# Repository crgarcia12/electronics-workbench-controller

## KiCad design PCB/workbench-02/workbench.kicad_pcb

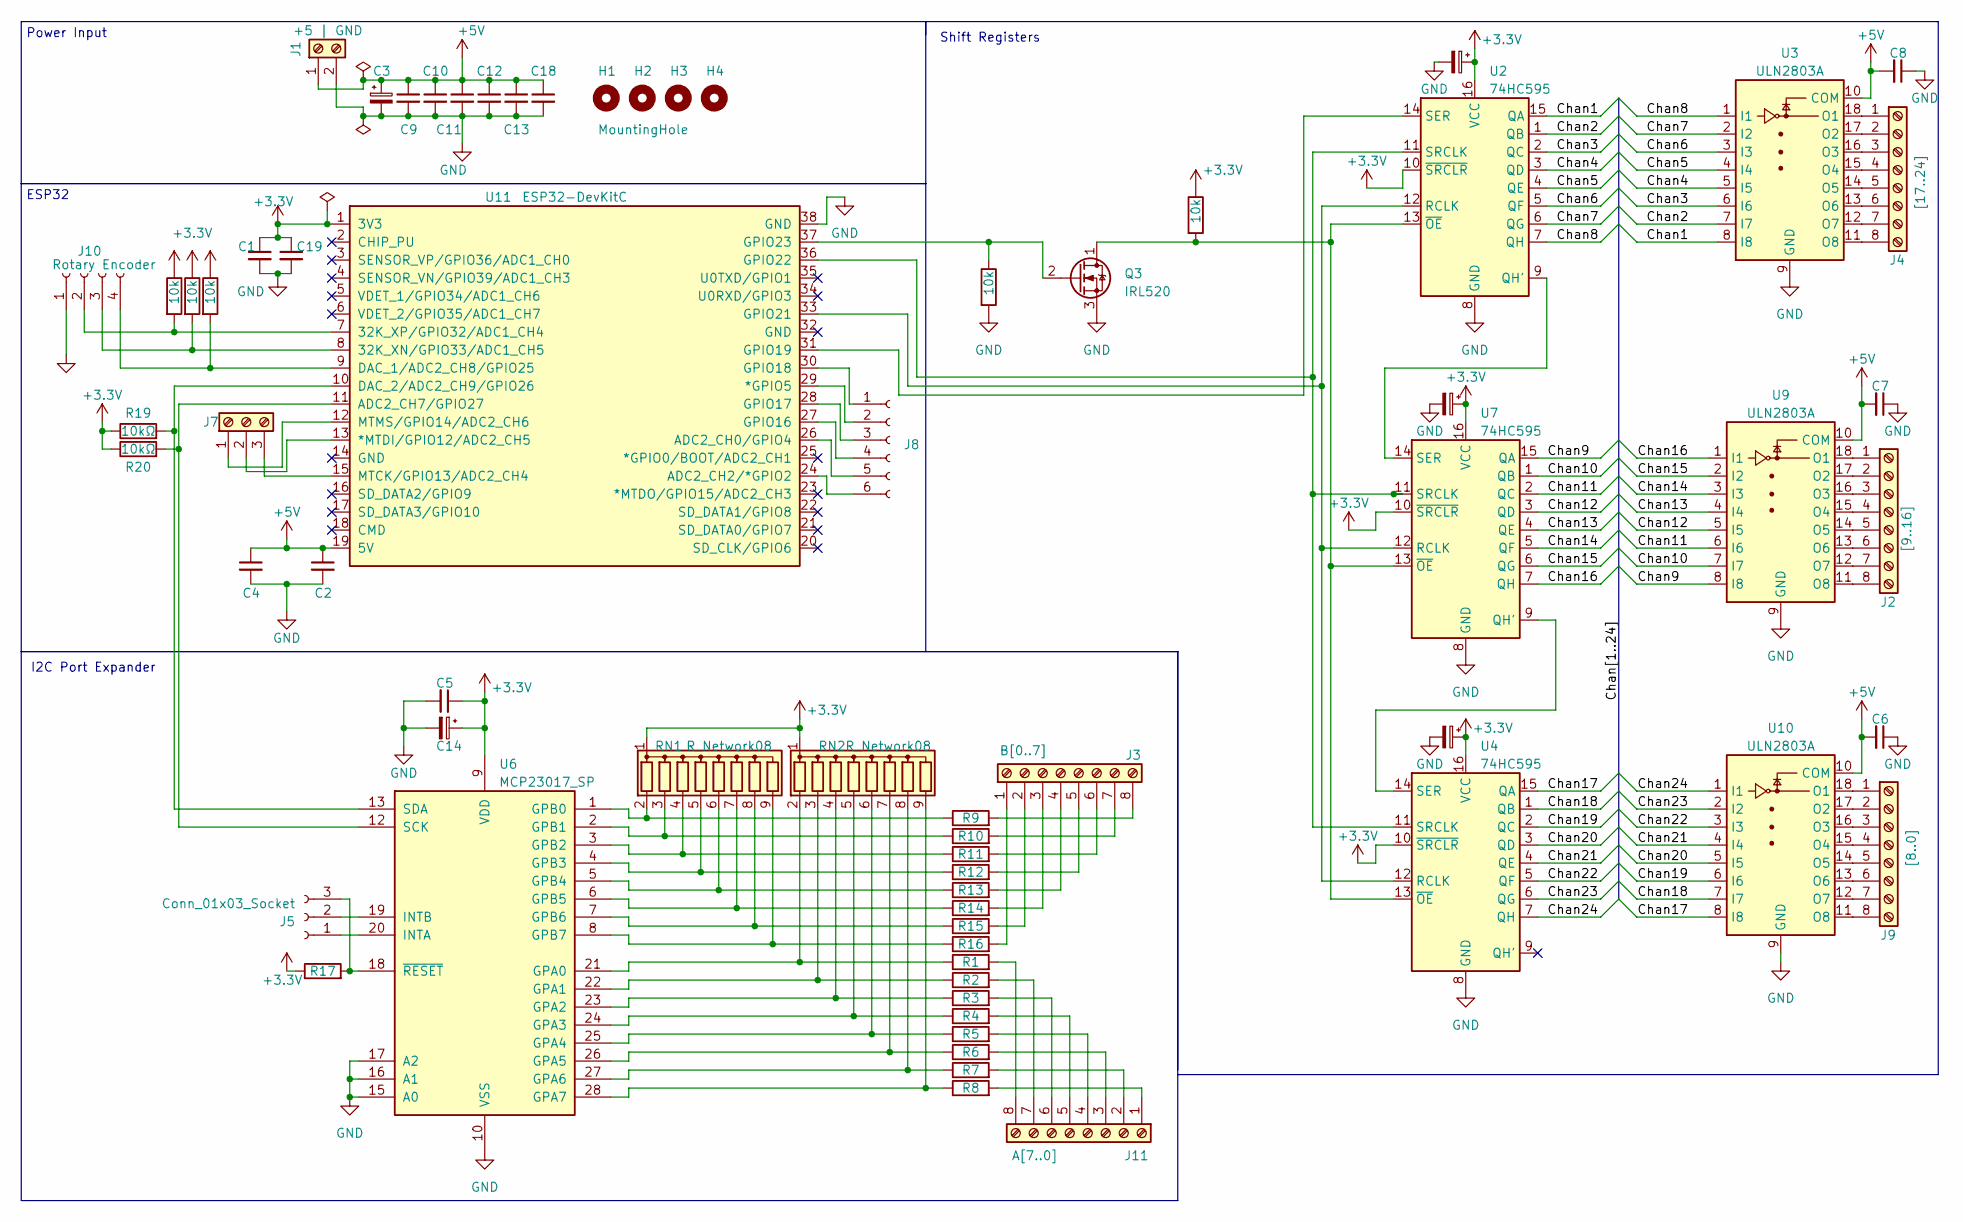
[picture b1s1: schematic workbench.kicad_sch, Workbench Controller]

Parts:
C1, C2: C; C_Disc_D5.1mm_W3.2mm_P5.00mm
C3, C14, C15, C16, C17: 10uF; CP_Radial_D6.3mm_P2.50mm
C4, C5, C6, C7, C8, C9, C10, C11, C12, C13, C18, C19: C; C_1210_3225Metric_Pad1.33x2.70mm_HandSolder
H1, H2, H4: MountingHole; MountingHole_4.3mm_M4_Pad_Via
H3: MountingHole; MountingHole_4.3mm_M4_DIN965_Pad
J1: +5 | GND; TerminalBlock_Phoenix_MKDS-3-2-5.08_1x02_P5.08mm_Horizontal
J2: [9..16]; TerminalBlock_Phoenix_MKDS-3-8-5.08_1x08_P5.08mm_Horizontal
J3: B[0..7]; TerminalBlock_Phoenix_MKDS-3-8-5.08_1x08_P5.08mm_Horizontal
J4: [17..24]; TerminalBlock_Phoenix_MKDS-3-8-5.08_1x08_P5.08mm_Horizontal
J5: Conn_01x03_Socket; PinHeader_1x03_P2.54mm_Vertical
J7: Led-13-12-14; TerminalBlock_Phoenix_MKDS-3-3-5.08_1x03_P5.08mm_Horizontal
J8: Conn_01x06_Socket; PinHeader_1x06_P2.54mm_Vertical
J9: [8..0]; TerminalBlock_Phoenix_MKDS-3-8-5.08_1x08_P5.08mm_Horizontal
J10: Rotary Encoder; TerminalBlock_Phoenix_MKDS-3-4-5.08_1x04_P5.08mm_Horizontal
J11: A[7..0]; TerminalBlock_Phoenix_MKDS-3-8-5.08_1x08_P5.08mm_Horizontal
Q3: IRL520; TO-220-3_Vertical
R1, R2, R3, R4, R5, R6, R7, R8, R9, R10, R11, R12, R13, R14, R15, R16, R17: R; R_Axial_DIN0207_L6.3mm_D2.5mm_P7.62mm_Horizontal
R19, R20: 10kΩ; R_Axial_DIN0207_L6.3mm_D2.5mm_P7.62mm_Horizontal; JLCPCB C25804
R21, R22, R35, R52, R53: 10k; R_Axial_DIN0207_L6.3mm_D2.5mm_P7.62mm_Horizontal
RN1, RN2: R_Network08; R_Array_SIP9
U2, U4, U7: 74HC595; DIP-16_W7.62mm_Socket_LongPads
U3, U9, U10: ULN2803A; DIP-18_W7.62mm_LongPads
U6: MCP23017_SP; DIP-28_W7.62mm
U11: ESP32-DevKitC

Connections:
+3.3V: C1.1, C5.1, C14.1, C15.1, C16.1, C17.1, C19.1, R17.1, R19.1, R20.1, R21.1, R22.1, R35.1, R53.1, RN1.1 (common), RN2.1 (common), U2.10 (~SRCLR), U2.16 (VCC), U4.10 (~SRCLR), U4.16 (VCC), U6.9 (VDD), U7.10 (~SRCLR), U7.16 (VCC), U11.1 (3V3)
+5V: C2.1, C3.1, C4.1, C6.2, C7.2, C8.2, C9.1, C10.1, C11.1, C12.1, C13.1, C18.1, J1.1, U3.10 (COM), U9.10 (COM), U10.10 (COM), U11.19 (5V)
/Chan1: U2.15 (QA), U3.8 (I8)
/Chan2: U2.1 (QB), U3.7 (I7)
/Chan3: U2.2 (QC), U3.6 (I6)
/Chan4: U2.3 (QD), U3.5 (I5)
/Chan5: U2.4 (QE), U3.4 (I4)
/Chan6: U2.5 (QF), U3.3 (I3)
/Chan7: U2.6 (QG), U3.2 (I2)
/Chan8: U2.7 (QH), U3.1 (I1)
/Chan9: U7.15 (QA), U9.8 (I8)
/Chan10: U7.1 (QB), U9.7 (I7)
/Chan11: U7.2 (QC), U9.6 (I6)
/Chan12: U7.3 (QD), U9.5 (I5)
/Chan13: U7.4 (QE), U9.4 (I4)
/Chan14: U7.5 (QF), U9.3 (I3)
/Chan15: U7.6 (QG), U9.2 (I2)
/Chan16: U7.7 (QH), U9.1 (I1)
/Chan17: U4.15 (QA), U10.8 (I8)
/Chan18: U4.1 (QB), U10.7 (I7)
/Chan19: U4.2 (QC), U10.6 (I6)
/Chan20: U4.3 (QD), U10.5 (I5)
/Chan21: U4.4 (QE), U10.4 (I4)
/Chan22: U4.5 (QF), U10.3 (I3)
/Chan23: U4.6 (QG), U10.2 (I2)
/Chan24: U4.7 (QH), U10.1 (I1)
GND: C1.2, C2.2, C3.2, C4.2, C5.2, C6.1, C7.1, C8.1, C9.2, C10.2, C11.2, C12.2, C13.2, C14.2, C15.2, C16.2, C17.2, C18.2, C19.2, J1.2, J10.1, Q3.3 (S), R52.2, U2.8 (GND), U3.9 (GND), U4.8 (GND), U6.10 (VSS), U6.15 (A0), U6.16 (A1), U6.17 (A2), U7.8 (GND), U9.9 (GND), U10.9 (GND), U11.38 (GND)
unnamed: J2.1, U9.18 (O1)
unnamed: J2.2, U9.17 (O2)
unnamed: J2.3, U9.16 (O3)
unnamed: J2.4, U9.15 (O4)
unnamed: J2.5, U9.14 (O5)
unnamed: J2.6, U9.13 (O6)
unnamed: J2.7, U9.12 (O7)
unnamed: J2.8, U9.11 (O8)
unnamed: J3.1, R16.2
unnamed: J3.2, R15.2
unnamed: J3.3, R14.2
unnamed: J3.4, R13.2
unnamed: J3.5, R12.2
unnamed: J3.6, R11.2
unnamed: J3.7, R10.2
unnamed: J3.8, R9.2
unnamed: J4.1, U3.18 (O1)
unnamed: J4.2, U3.17 (O2)
unnamed: J4.3, U3.16 (O3)
unnamed: J4.4, U3.15 (O4)
unnamed: J4.5, U3.14 (O5)
unnamed: J4.6, U3.13 (O6)
unnamed: J4.7, U3.12 (O7)
unnamed: J4.8, U3.11 (O8)
unnamed: J5.1, U6.20 (INTA)
unnamed: J5.2, U6.19 (INTB)
unnamed: J5.3, R17.2, U6.18 (~RESET)
unnamed: J7.1, U11.12 (MTMS/GPIO14/ADC2_CH6)
unnamed: J7.2, U11.13 (*MTDI/GPIO12/ADC2_CH5)
unnamed: J7.3, U11.15 (MTCK/GPIO13/ADC2_CH4)
unnamed: J8.1, U11.30 (GPIO18)
unnamed: J8.2, U11.29 (*GPIO5)
unnamed: J8.3, U11.28 (GPIO17)
unnamed: J8.4, U11.27 (GPIO16)
unnamed: J8.5, U11.26 (ADC2_CH0/GPIO4)
unnamed: J8.6, U11.24 (ADC2_CH2/*GPIO2)
unnamed: J9.1, U10.18 (O1)
unnamed: J9.2, U10.17 (O2)
unnamed: J9.3, U10.16 (O3)
unnamed: J9.4, U10.15 (O4)
unnamed: J9.5, U10.14 (O5)
unnamed: J9.6, U10.13 (O6)
unnamed: J9.7, U10.12 (O7)
unnamed: J9.8, U10.11 (O8)
unnamed: J10.2, R21.2, U11.7 (32K_XP/GPIO32/ADC1_CH4)
unnamed: J10.3, R22.2, U11.8 (32K_XN/GPIO33/ADC1_CH5)
unnamed: J10.4, R35.2, U11.9 (DAC_1/ADC2_CH8/GPIO25)
unnamed: J11.1, R8.2
unnamed: J11.2, R7.2
unnamed: J11.3, R6.2
unnamed: J11.4, R5.2
unnamed: J11.5, R4.2
unnamed: J11.6, R3.2
unnamed: J11.7, R2.2
unnamed: J11.8, R1.2
unnamed: Q3.1 (D), R53.2, U2.13 (~OE), U4.13 (~OE), U7.13 (~OE)
unnamed: Q3.2 (G), R52.1, U11.37 (GPIO23)
unnamed: R9.1, RN1.2 (R1), U6.1 (GPB0)
unnamed: R10.1, RN1.3 (R2), U6.2 (GPB1)
unnamed: R11.1, RN1.4 (R3), U6.3 (GPB2)
unnamed: R12.1, RN1.5 (R4), U6.4 (GPB3)
unnamed: R13.1, RN1.6 (R5), U6.5 (GPB4)
unnamed: R14.1, RN1.7 (R6), U6.6 (GPB5)
unnamed: R15.1, RN1.8 (R7), U6.7 (GPB6)
unnamed: R16.1, RN1.9 (R8), U6.8 (GPB7)
unnamed: R1.1, RN2.2 (R1), U6.21 (GPA0)
unnamed: R2.1, RN2.3 (R2), U6.22 (GPA1)
unnamed: R3.1, RN2.4 (R3), U6.23 (GPA2)
unnamed: R4.1, RN2.5 (R4), U6.24 (GPA3)
unnamed: R5.1, RN2.6 (R5), U6.25 (GPA4)
unnamed: R6.1, RN2.7 (R6), U6.26 (GPA5)
unnamed: R7.1, RN2.8 (R7), U6.27 (GPA6)
unnamed: R8.1, RN2.9 (R8), U6.28 (GPA7)
unnamed: U2.9 (QH'), U7.14 (SER)
unnamed: U4.14 (SER), U7.9 (QH')
unnamed: R20.2, U6.12 (SCK), U11.11 (ADC2_CH7/GPIO27)
unnamed: R19.2, U6.13 (SDA), U11.10 (DAC_2/ADC2_CH9/GPIO26)
unnamed: U2.14 (SER), U11.31 (GPIO19)
unnamed: U2.12 (RCLK), U4.12 (RCLK), U7.12 (RCLK), U11.33 (GPIO21)
unnamed: U2.11 (SRCLK), U4.11 (SRCLK), U7.11 (SRCLK), U11.36 (GPIO22)

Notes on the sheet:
ESP32
Power Input
Shift Registers
I2C Port Expander

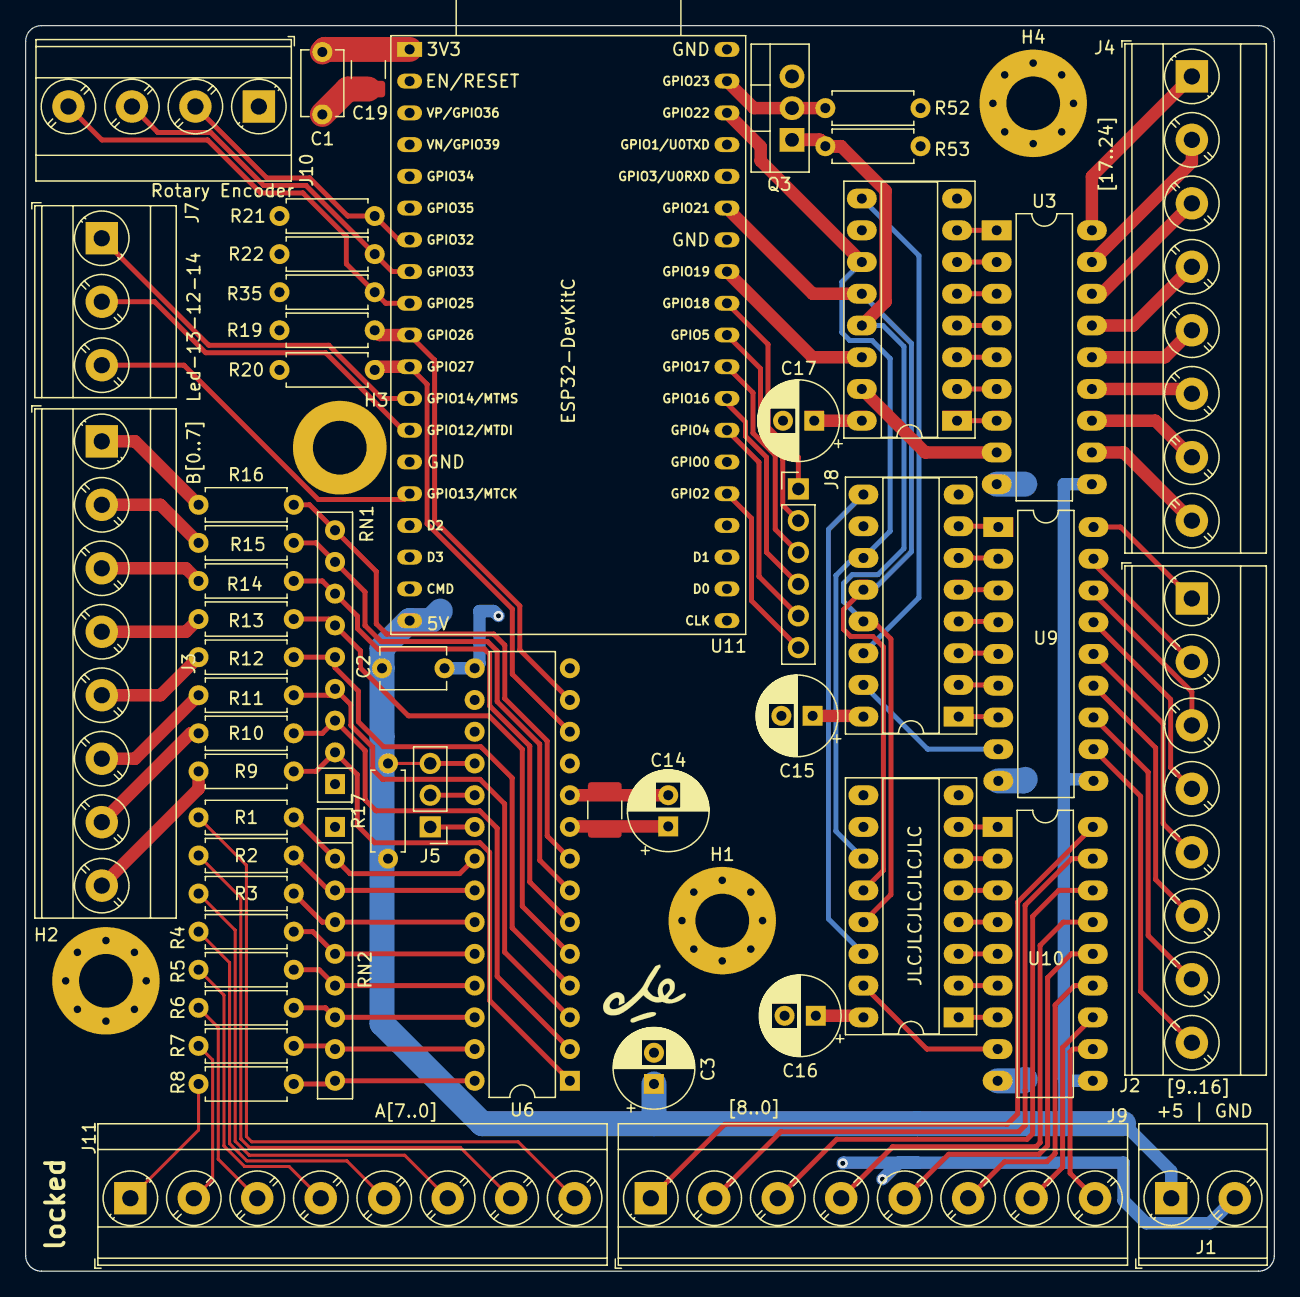
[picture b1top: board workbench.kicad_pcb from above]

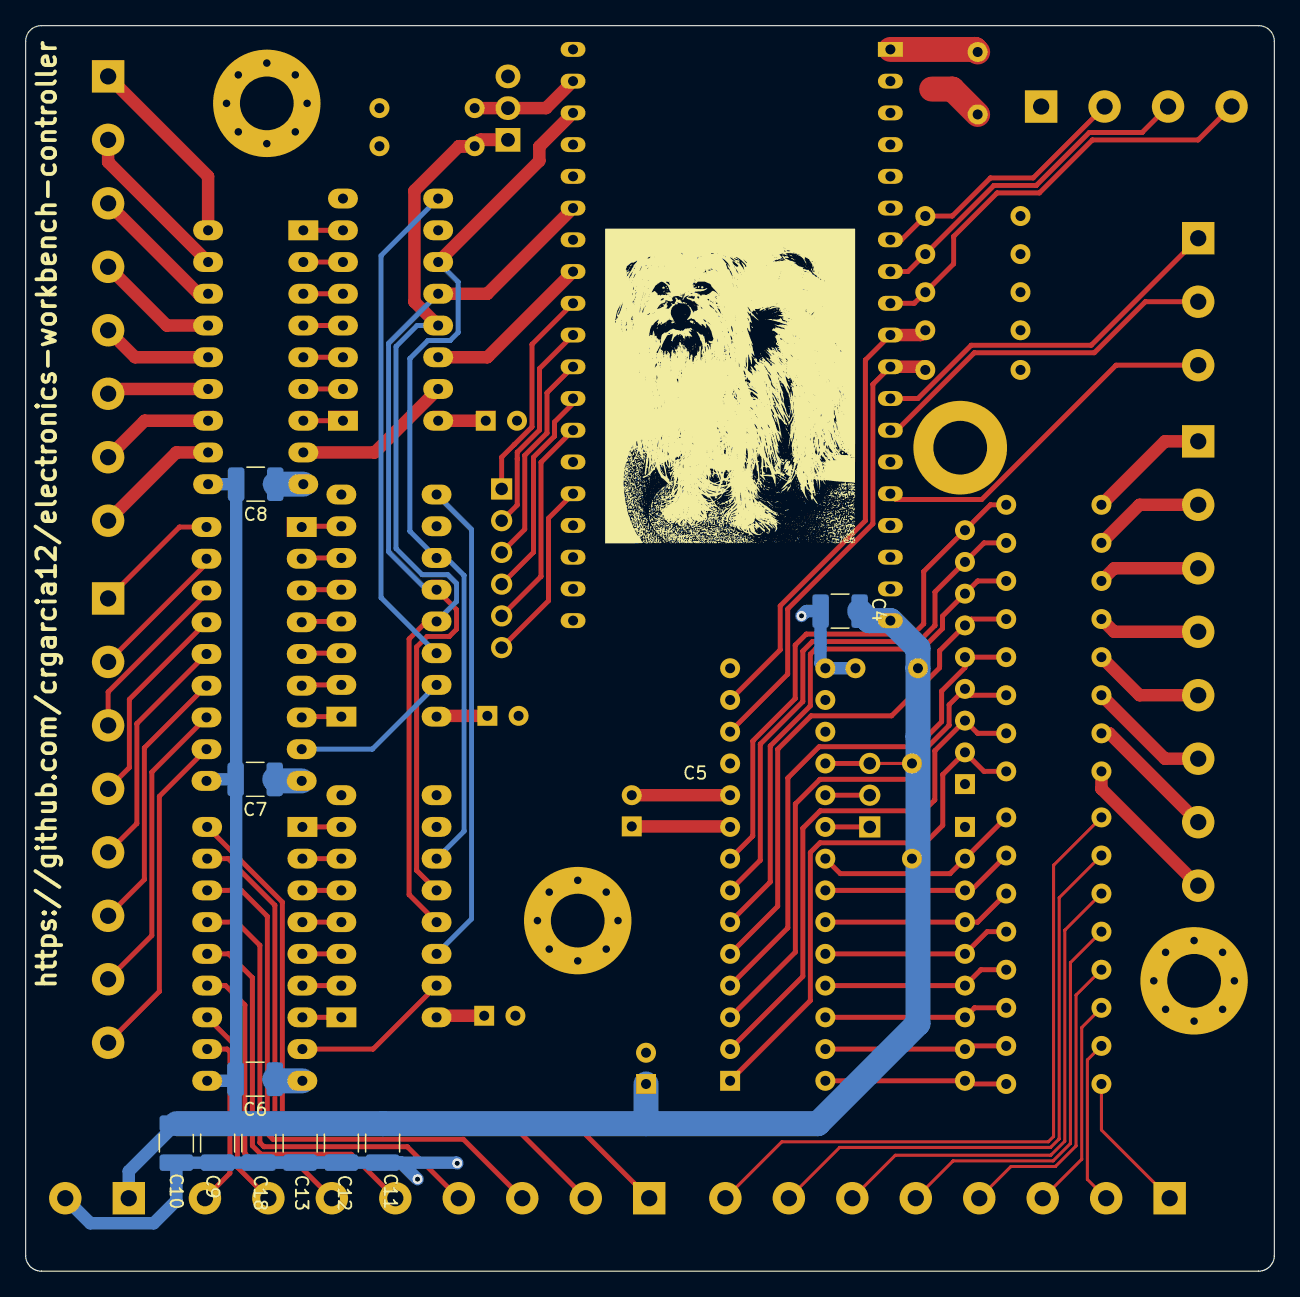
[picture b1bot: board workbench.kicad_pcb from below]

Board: 4 copper layers, 99.9 x 99.7 mm, 68 parts (10 on the bottom side), 107 nets.

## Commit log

2023-05-26 initial project
2023-05-27 adding pins for Leds. Silkscreen. logos. production files
2023-05-27 adding a readme
2023-05-27 V01 to JLC
2023-05-27 updating readme
2023-05-27 Adding some text into the readme
2023-05-29 adding v2, which contains pullup resistor from MCP23017.Reset to e.eV
2023-06-05 arduino code
2024-02-11 adding few more images
